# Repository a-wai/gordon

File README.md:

# gordon

*gordon* is a Flash memory programmer shield for the ST Nucleo-F401RE board
(pin-compatible with Nucleo-F411RE and Nucleo-F446RE), chosen because of its
numerous, 5V-tolerant, GPIO pins.

## Licensing

Copyright 2019, Arnaud Ferraris.

This documentation describes Open Hardware and is licensed under the
CERN OHL v.1.2.

You may redistribute and modify this documentation under the terms of the
[CERN OHL v.1.2](http://ohwr.org/cernohl). This documentation is distributed
WITHOUT ANY EXPRESS OR IMPLIED WARRANTY, INCLUDING OF MERCHANTABILITY,
SATISFACTORY QUALITY AND FITNESS FOR A PARTICULAR PURPOSE.

Please see the CERN OHL v.1.2 for applicable conditions.

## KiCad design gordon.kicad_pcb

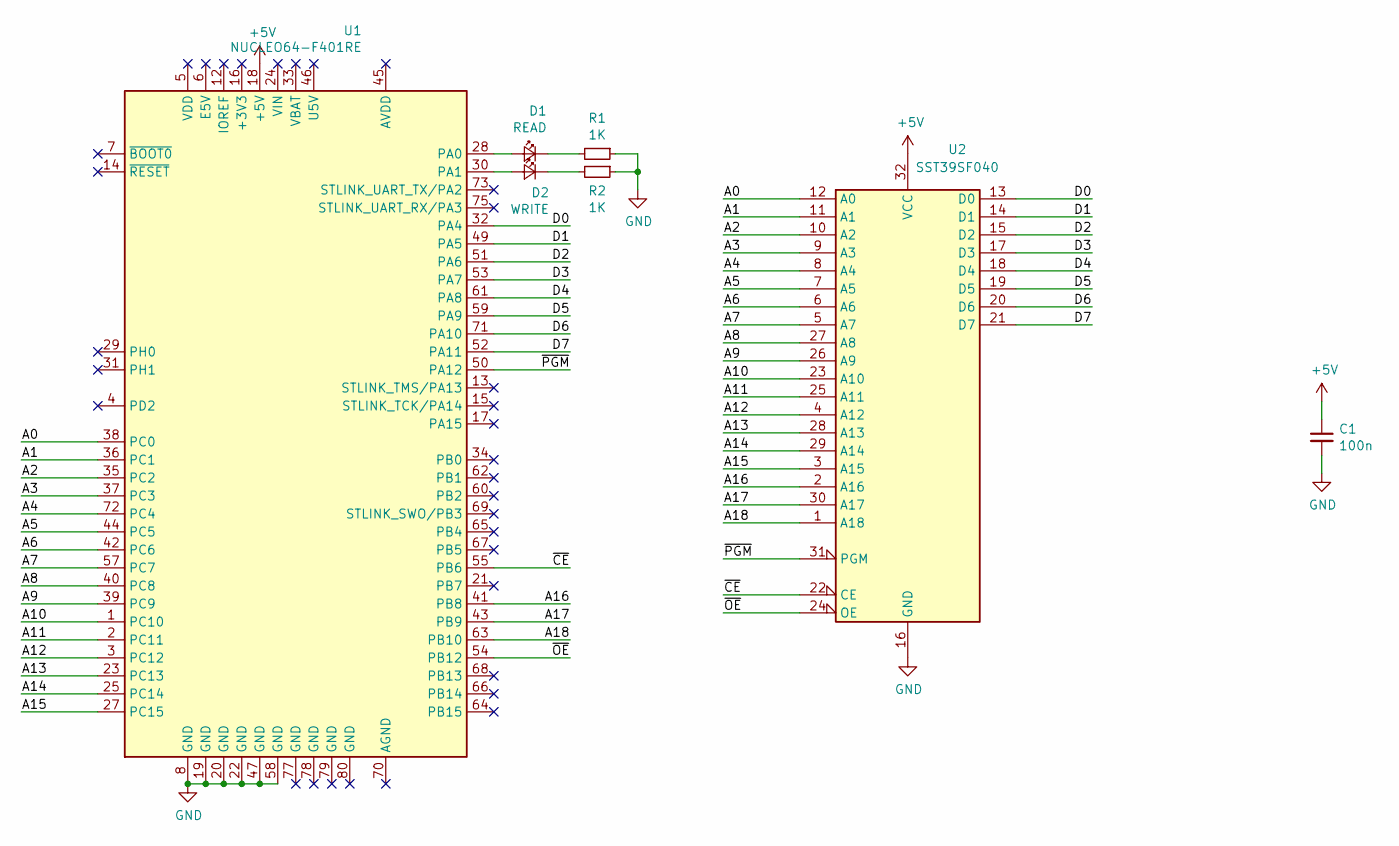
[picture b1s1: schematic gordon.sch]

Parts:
C1: 100n; C_Disc_D3.8mm_W2.6mm_P2.50mm
D1: READ; LED_D3.0mm
D2: WRITE; LED_D3.0mm
R1, R2: 1K; R_Axial_DIN0207_L6.3mm_D2.5mm_P7.62mm_Horizontal
U1: NUCLEO64-F401RE; ST_Morpho_Connector_64_STLink
U2: SST39SF040; DIP_Socket-32_W11.9_W12.7_W15.24_W17.78_W18.5_3M_232-1285-0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

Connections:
+5V: C1.1, U1.18 (+5V), U2.32 (VCC)
/A0: U1.38 (PC0), U2.12 (A0)
/A1: U1.36 (PC1), U2.11 (A1)
/A2: U1.35 (PC2), U2.10 (A2)
/A3: U1.37 (PC3), U2.9 (A3)
/A4: U1.72 (PC4), U2.8 (A4)
/A5: U1.44 (PC5), U2.7 (A5)
/A6: U1.42 (PC6), U2.6 (A6)
/A7: U1.57 (PC7), U2.5 (A7)
/A8: U1.40 (PC8), U2.27 (A8)
/A9: U1.39 (PC9), U2.26 (A9)
/A10: U1.1 (PC10), U2.23 (A10)
/A11: U1.2 (PC11), U2.25 (A11)
/A12: U1.3 (PC12), U2.4 (A12)
/A13: U1.23 (PC13), U2.28 (A13)
/A14: U1.25 (PC14), U2.29 (A14)
/A15: U1.27 (PC15), U2.3 (A15)
/A16: U1.41 (PB8), U2.2 (A16)
/A17: U1.43 (PB9), U2.30 (A17)
/A18: U1.63 (PB10), U2.1 (A18)
/D0: U1.32 (PA4), U2.13 (D0)
/D1: U1.49 (PA5), U2.14 (D1)
/D2: U1.51 (PA6), U2.15 (D2)
/D3: U1.53 (PA7), U2.17 (D3)
/D4: U1.61 (PA8), U2.18 (D4)
/D5: U1.59 (PA9), U2.19 (D5)
/D6: U1.71 (PA10), U2.20 (D6)
/D7: U1.52 (PA11), U2.21 (D7)
/~CE: U1.55 (PB6), U2.22 (CE)
/~OE: U1.54 (PB12), U2.24 (OE)
/~PGM: U1.50 (PA12), U2.31 (PGM)
GND: C1.2, R1.1, R2.1, U1.8 (GND), U1.19 (GND), U1.20 (GND), U1.22 (GND), U1.47 (GND), U1.58 (GND), U2.16 (GND)
unnamed: D1.1 (K), R1.2
unnamed: D1.2 (A), U1.28 (PA0)
unnamed: D2.1 (K), R2.2
unnamed: D2.2 (A), U1.30 (PA1)

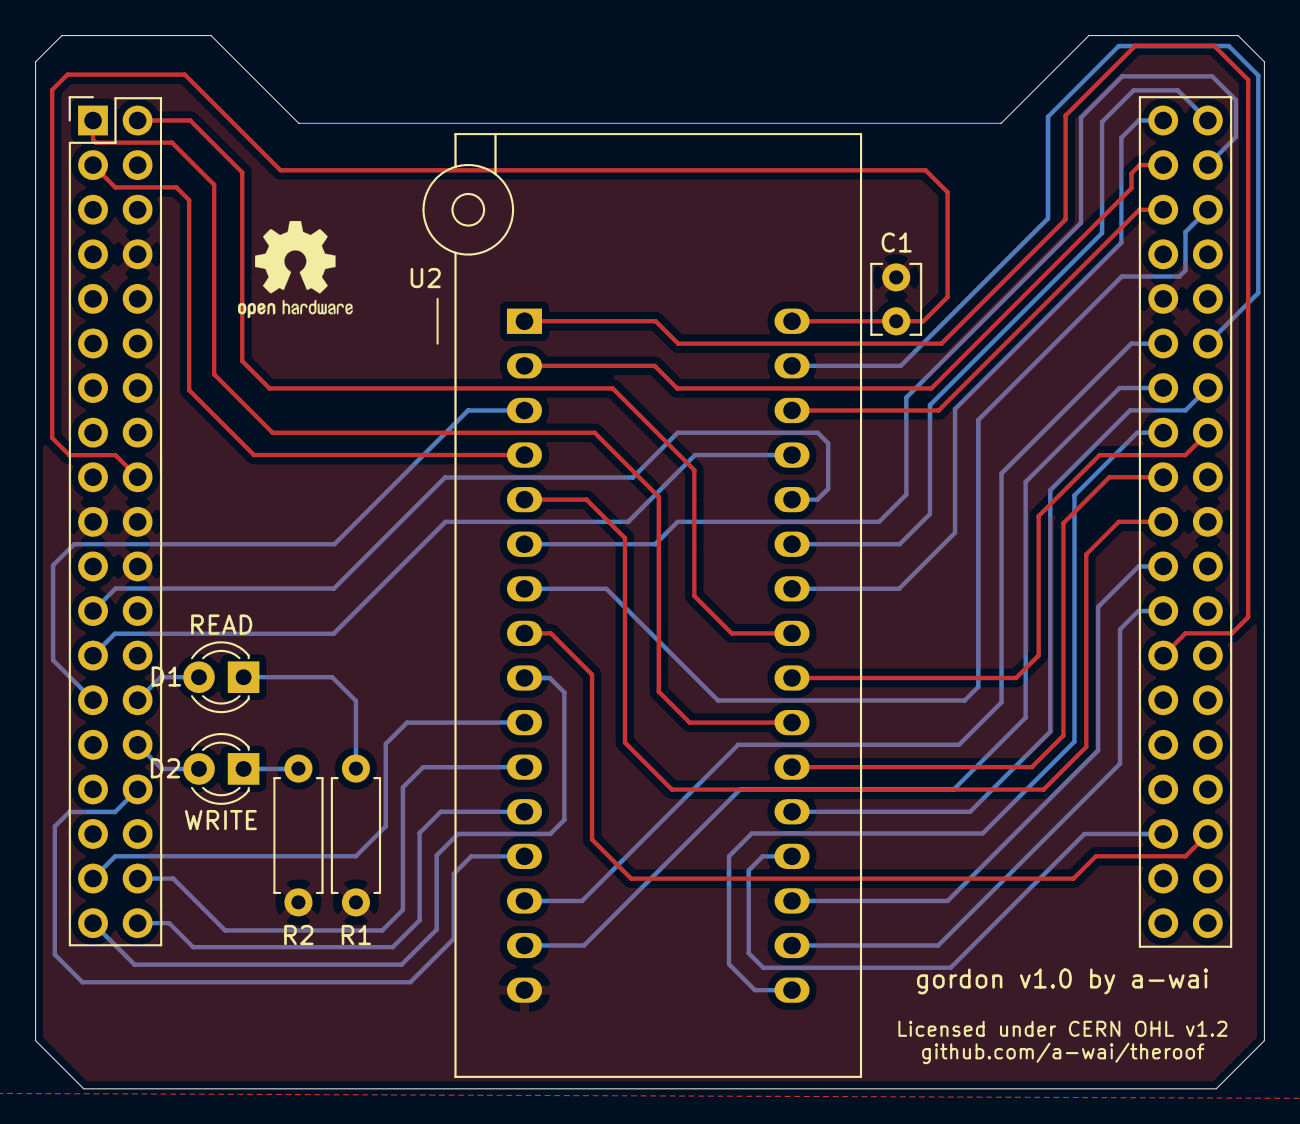
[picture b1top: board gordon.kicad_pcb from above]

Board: 2 copper layers, 70.0 x 60.0 mm, 7 parts (0 on the bottom side), 36 nets.

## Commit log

2019-11-28 Improve routing of A4 line
2019-11-28 Add gerber files

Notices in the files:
gordon.kicad_pcb:
Licensed under CERN OHL v1.2
